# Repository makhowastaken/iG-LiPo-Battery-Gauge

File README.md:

# iG-LiPo-Battery-Gauge
Modified version of https://github.com/insidegadgets/LiPo-Battery-Gauge

I made this because I accidentally ordered the wrong ATTINYs and it was cheaper to make new custom PCBs than to order the correct MCUs. I also tweaked the LED board that Alex uploaded to comply with OSHpark's minimum size requirements. 

## LED Board

I've uploaded the tweaked EAGLE BRD file and uploaded the exported gerbers if you want to use a different manufacturer. This PCB fits nicely in a GBA right below the LCD. See [my youtube video](https://www.youtube.com/watch?v=7A705K_WF-E) for more info on the install and usage.

[Order the LED board here](https://oshpark.com/shared_projects/lczB1jHZ)

## Main Board

I recreated the original main board for use with a different size ATTINY. This is functionally identical to Alex's board and other than the ATTINY, it uses the exact same parts. You can also solder resistors and LEDs straight to this board but I think some tweaks to this board would make that a lot easier. 
[Order the LED board here](https://oshpark.com/shared_projects/5IOiieSn)

## BOM

The BOM (Bill of Materials) is inside the EAGLE schematic files for the original PCBs ([see the linked repo](https://github.com/insidegadgets/LiPo-Battery-Gauge)) but I'll sum everything up for you: 

LED Board
* 10x 10k SMT 0805 resistors (or 0603, both fit fine)
* 10x 1206 SMT LEDs in whatever color you want

Main Board -- all resistor and capacitor pads are sized for 0603 components but are slightly oversized for hand soldering and will take a 0805 component on a whim. 
* 3x 0603 0.1uF capacitors
* 1x 10K 0603 resistor (R6)
* 1x 320K 0603 resistor (R7) (though the firmware I uploaded is for if you use a 300k resistor instead)
* 1x 1M 0603 resistor (R2)
* 1x ATTINY48 VQFN-28 package for Alex's board or QFP-32 for my board 

## Firmware 

The firmware in this repo is for if you use a 300k resistor instead of a 320k resistor. Otherwise, your gauge will estimate incorrectly. I have also tweaked the firmware to change the scale so that nearly full charge illumunates all 10 LEDs and nearly empty charge disabled all 10 LEDs. It should scale somewhat linearly but battery voltage curves can be weird. 

Editing the firmware? Good luck. I added comments for the SP version of the firmware regarding the values I tweaked. I did not do the same for the GBA version as I didn't intend on sharing it. My bad. I used ubuntu for editing and recompiling. I've also already tweaked the makefiles so once you have all the dependencies, you'll just need to run make and take the .hex file and flash that to your ATTINY with avrdude. If compiling with Windows, you'll have to edit the makefile to include the location of the binaries or just add all the binaries to your PATH file. 

As far as flashing the firmware goes, I used avrdude, a USBasp, and Windows for that. I used zadig to install the libusb-win32 driver for my USBasp instead of the default one Windows installs. Otherwise, avrdude won't recognize the USBasp. Once setup, you'll need to download avrdude and the main.hex file from the insideGadgets repo or my repo and run the following command: .\avrdude.exe -c usbasp -p attiny48 -u -U flash:w:main.hex and you'll probably have to add some lines to your avrdude.conf file just to get it flash an attiny48. This worked for me: https://lists.nongnu.org/archive/html/avrdude-dev/2009-08/msg00005.html

I've also attached my avrdude.conf file for reference. It needs to be in the same directory as avrdude to work. 

## Installation

Assemble the boards, flash the firmware, TEST FIT your preferred location, then stick both boards down. You'll have to connect the LED board to the main board with 11 wires (10 LED, 1 common ground). I know this sounds obvious, but don't forget to account for the thickness of wire. 30 AWG solid core works fine for this though thinner might be better. Sorry for the vague instructions but connecting the two boards is a subjective process. My video linked earlier shows how I did it.

You'll also need to connect the main board to the Game Boy with three wires. B- goes either directly on the negative battery terminal or the system ground. If there is a diode between your battery and the GBA on the battery terminal, the wire needs to go directly to the battery or the voltage will not measure correctly. B+ goes directly on the positive battery terminal though you can also connect it directly to the system fuse instead to protect the input of the gauge board if your diode is on the ground side. Lastly, the reference wire needs to be connected to the system power so that it is powered only when the system is on. The best spot is one of the two common pins on the power switch. Please see the diagram below for one such method of wiring up this board.

(base image from https://gbhwdb.gekkio.fi/consoles/agb/)

Keep in mind that there is no diode on this diagram. The B+ or B- wire **must** go on the battery side of the diode.

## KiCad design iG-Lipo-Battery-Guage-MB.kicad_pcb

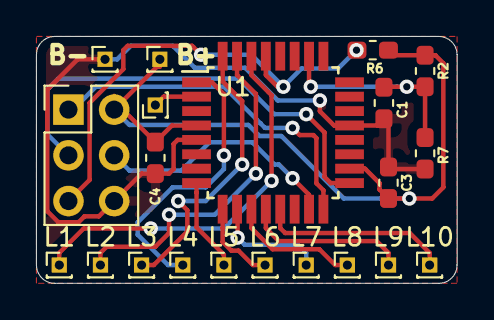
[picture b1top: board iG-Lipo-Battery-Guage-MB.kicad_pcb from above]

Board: 2 copper layers, 23.4 x 13.7 mm, 21 parts (0 on the bottom side), 18 nets.

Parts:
AFTER_POWER_SWITCH1: Conn_01x01; PinHeader_1x01_P1.00mm_Vertical
C1, C3, C4: 0.1uF; C_0603_1608Metric_Pad1.05x0.95mm_HandSolder
J1: AVR_SPI_6; PinHeader_2x03_P2.54mm_Vertical
L1, L2, L3, L4, L5, L6, L7, L8, L9, L10: Conn_01x01; PinHeader_1x01_P1.00mm_Vertical
LIPO+1: Conn_01x01; PinHeader_1x01_P1.00mm_Vertical
LIPO-1: Conn_01x01; PinHeader_1x01_P1.00mm_Vertical
R2: 1M; R_0603_1608Metric_Pad1.05x0.95mm_HandSolder
R6: 10K; R_0603_1608Metric_Pad1.05x0.95mm_HandSolder
R7: 320K; R_0603_1608Metric_Pad1.05x0.95mm_HandSolder
U1: ATtiny48-AU; TQFP-32_7x7mm_P0.8mm

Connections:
GND: C1.2, C3.2, C4.1, J1.6, LIPO-1.1, R7.2, U1.5, U1.21
MISO: J1.1, U1.16
MOSI: J1.4, U1.15
unnamed: AFTER_POWER_SWITCH1.1, U1.2
unnamed: C1.1, R2.2, R7.1, U1.26
unnamed: L1.1, U1.30
unnamed: L2.1, U1.31
unnamed: L3.1, U1.32
unnamed: L4.1, U1.1
unnamed: L5.1, U1.8
unnamed: L6.1, U1.9
unnamed: L7.1, U1.10
unnamed: L8.1, U1.11
unnamed: L9.1, U1.12
unnamed: L10.1, U1.13
RESET: J1.5, R6.2, U1.29
SCK: J1.3, U1.17
VCC: C3.1, C4.2, J1.2, LIPO+1.1, R2.1, R6.1, U1.4, U1.18
